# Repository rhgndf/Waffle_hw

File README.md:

# Waffle: a pocket pager, LoRA transceiver and RF experimentation platform
Hardware designs for Waffle, a compact Pager and general RF multitool.

## Introduction
This is a reboot of a [project started in 2016](https://hackaday.io/project/11056-waffle-a-pocket-sized-digital-radio-system), aimed at creating a pocket-sized digital radio system. Due to a lack of clear objectives and motivation, this project never got any further. However, there is today a certain revival of POCSAG in the amateur radio community, with the [DAPNET project](http://hampager.de). No open-source pager design exist to this day. This project aims to bridge that gap, and bring an open design that could be adapted to anyone's needs. 

## Feature list

 - UHF (430-440) support
 - User interface with three buttons and an easy-to-read display
 - Programmable either via the display, or via Wifi and web portal. 

## Hardware
Uses an ESP32-S3, coupled with an SX1276 for reception and transmission of signals. Battery is a classic 3.7V Li-Ion cell with integrated battery management and charging. USB-C port for programming and charging. OLED or LCD display (TBD).

## Hardware revision list

 - The [initial design from 2016](https://hackaday.io/project/11056-waffle-a-pocket-sized-digital-radio-system) is known as rev XX
 - 0.1a: current version. Aims to validate the basic hardware choices and being dev on software.

## Software
The (WIP) software can be found in [this repository](https://github.com/Jankyneering/Waffle_sw).

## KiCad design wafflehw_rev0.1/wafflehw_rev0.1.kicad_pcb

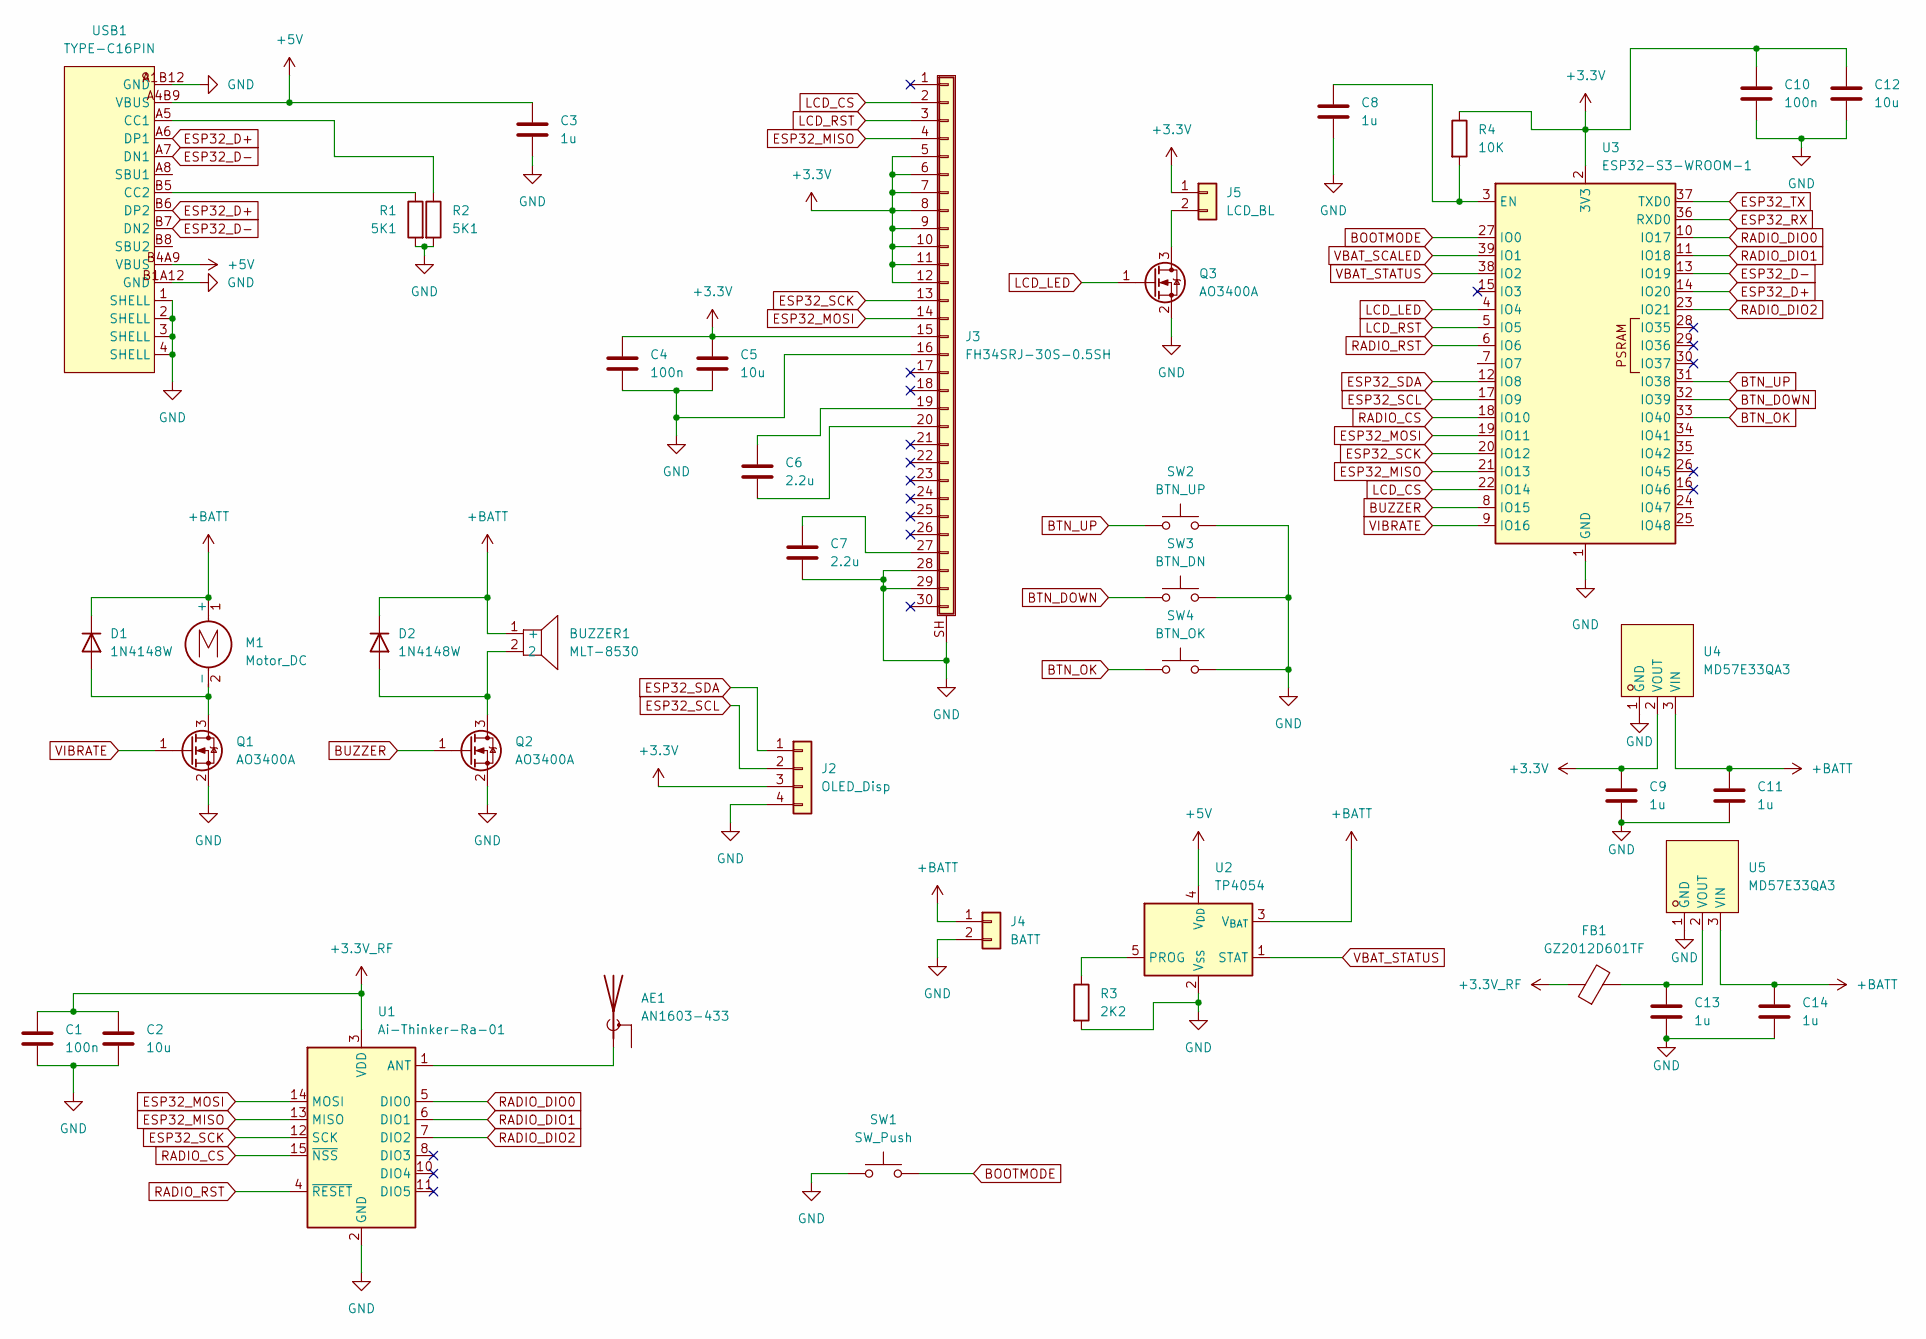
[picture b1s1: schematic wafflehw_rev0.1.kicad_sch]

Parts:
AE1: AN1603-433; Coilcraft_MA5532-AE_RFID
BUZZER1: MLT-8530; BUZ-SMD_4P-L8.5-W8.5-P8.50-BR; LCSC Part C94599
C1, C4, C10: 100n; C_0805_2012Metric
C2, C5, C12: 10u; C_0805_2012Metric
C3, C8, C9, C11, C13, C14: 1u; C_0805_2012Metric
C6, C7: 2.2u; C_0805_2012Metric
D1, D2: 1N4148W; D_SOD-123
FB1: GZ2012D601TF; L_0805_2012Metric
J2: OLED_Disp; PinHeader_1x04_P2.54mm_Vertical
J3: FH34SRJ-30S-0.5SH; ER-CON30HB-1
J4: BATT; ER-CON2.0-2P-SMD
J5: LCD_BL; ER-CON2.0-2P-SMD
M1: Motor_DC
Q1, Q2, Q3: AO3400A; SOT-23
R1, R2: 5K1; C_0805_2012Metric
R3: 2K2; C_0805_2012Metric
R4: 10K; C_0805_2012Metric
SW1: SW_Push; SW_SPST_CK_RS282G05A3
SW2: BTN_UP; SW_SPST_CK_RS282G05A3
SW3: BTN_DN; SW_SPST_CK_RS282G05A3
SW4: BTN_OK; SW_SPST_CK_RS282G05A3
U1: Ai-Thinker-Ra-01; Ai-Thinker-Ra-01-LoRa
U2: TP4054; SOT-23-5
U3: ESP32-S3-WROOM-1
U4, U5: MD57E33QA3; SOT-23-3_L2.9-W1.6-P1.90-LS2.8-BR; LCSC Part C920553
USB1: TYPE-C16PIN; USB-C-SMD_TYPE-C16PIN; LCSC Part C393939

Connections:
+3.3V: C4.1, C5.1, C9.1, C10.1, C12.1, J2.3, J3.5, J3.6, J3.7, J3.8, J3.9, J3.10, J3.11, J3.12, J3.15, J5.1, R4.1, U3.2 (3V3), U4.2 (VOUT)
+3.3V_RF: C1.1, C2.1, FB1.1, U1.3 (VDD)
+5V: C3.1, U2.4 (V_{DD}), USB1.A4B9 (VBUS), USB1.B4A9 (VBUS)
+BATT: BUZZER1.1 (+), C11.1, C14.1, D1.1 (K), D2.1 (K), J4.1, M1.1 (+), U2.3 (V_{BAT}), U4.3 (VIN), U5.3 (VIN)
BOOTMODE: SW1.2, U3.27 (IO0)
BTN_DOWN: SW3.1, U3.32 (IO39)
BTN_OK: SW4.1, U3.33 (IO40)
BTN_UP: SW2.1, U3.31 (IO38)
BUZZER: Q2.1 (G), U3.8 (IO15)
ESP32_D+: U3.14 (IO20), USB1.A6 (DP1), USB1.B6 (DP2)
ESP32_D-: U3.13 (IO19), USB1.A7 (DN1), USB1.B7 (DN2)
ESP32_MISO: J3.4, U1.13 (MISO), U3.21 (IO13)
ESP32_MOSI: J3.14, U1.14 (MOSI), U3.19 (IO11)
ESP32_RX: U3.36 (RXD0)
ESP32_SCK: J3.13, U1.12 (SCK), U3.20 (IO12)
ESP32_SCL: J2.2, U3.17 (IO9)
ESP32_SDA: J2.1, U3.12 (IO8)
ESP32_TX: U3.37 (TXD0)
GND: C1.2, C2.2, C3.2, C4.2, C5.2, C7.2, C8.2, C9.2, C10.2, C11.2, C12.2, C13.2, C14.2, J2.4, J3.16, J3.28, J3.29, J3.SH (Shield), J4.2, Q1.2 (S), Q2.2 (S), Q3.2 (S), R1.2, R2.2, R3.2, SW1.1, SW2.2, SW3.2, SW4.2, U1.2 (GND), U1.9 (GND), U1.16 (GND), U2.2 (V_{SS}), U3.1 (GND), U3.40 (GND), U3.41 (GND), U4.1 (GND), U5.1 (GND), USB1.1 (SHELL), USB1.2 (SHELL), USB1.3 (SHELL), USB1.4 (SHELL), USB1.A1B12 (GND), USB1.B1A12 (GND)
LCD_CS: J3.2, U3.22 (IO14)
LCD_LED: Q3.1 (G), U3.4 (IO4)
LCD_RST: J3.3, U3.5 (IO5)
unnamed: AE1.1 (A), U1.1 (ANT)
unnamed: D1.2 (A), M1.2 (-), Q1.3 (D)
unnamed: BUZZER1.2, D2.2 (A), Q2.3 (D)
unnamed: C6.1, J3.19
unnamed: C6.2, J3.20
unnamed: C7.1, J3.27
unnamed: J5.2, Q3.3 (D)
unnamed: R3.1, U2.5 (PROG)
unnamed: C8.1, R4.2, U3.3 (EN)
unnamed: C13.1, FB1.2, U5.2 (VOUT)
unnamed: R2.1, USB1.A5 (CC1)
unnamed: R1.1, USB1.B5 (CC2)
RADIO_CS: U1.15 (~NSS), U3.18 (IO10)
RADIO_DIO0: U1.5 (DIO0), U3.10 (IO17)
RADIO_DIO1: U1.6 (DIO1), U3.11 (IO18)
RADIO_DIO2: U1.7 (DIO2), U3.23 (IO21)
RADIO_RST: U1.4 (~RESET), U3.6 (IO6)
VBAT_SCALED: U3.39 (IO1)
VBAT_STATUS: U2.1 (STAT), U3.38 (IO2)
VIBRATE: Q1.1 (G), U3.9 (IO16)

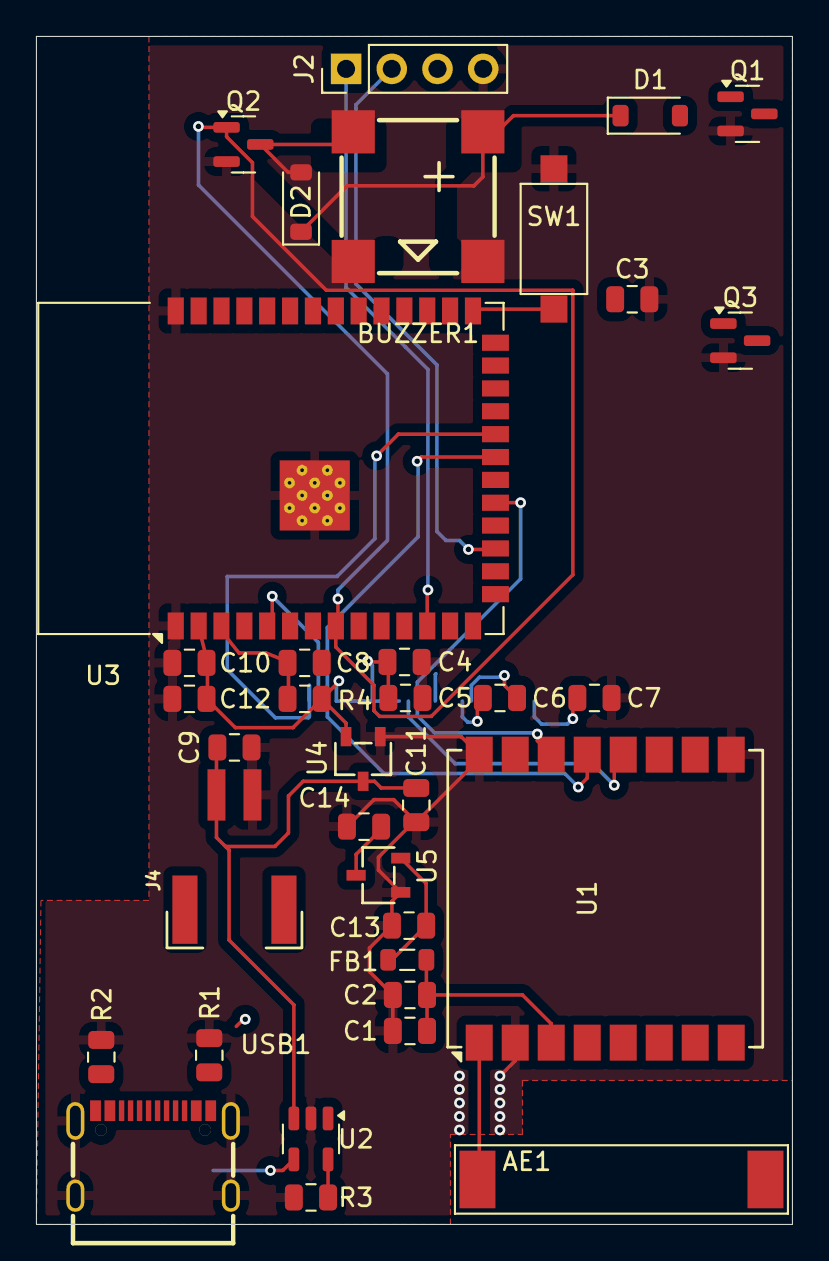
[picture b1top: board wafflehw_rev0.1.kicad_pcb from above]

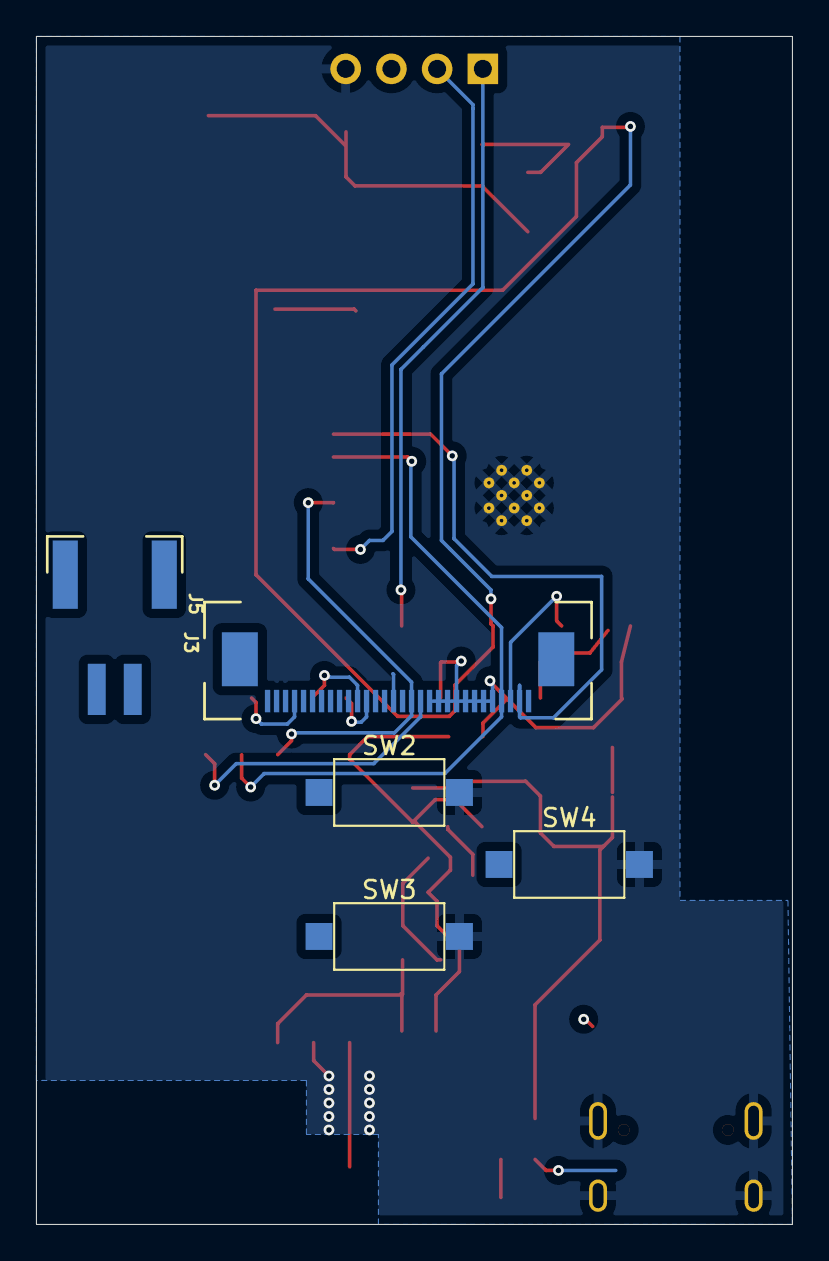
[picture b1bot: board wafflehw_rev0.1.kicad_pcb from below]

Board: 2 copper layers, 42.0 x 66.0 mm, 40 parts (5 on the bottom side), 39 nets.

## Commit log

2024-09-13 Initial Commit
    Added wip design for rev 0.1
2024-09-19 Schematic improvements
2024-09-19 Schematic improvements
    - Changed to two LDOs and add ferrite beads
    - Changed battery charging IC to pin compatible TP4054
    - USB connector changed to more common variant
    - Antenna pad disconnected from ground
